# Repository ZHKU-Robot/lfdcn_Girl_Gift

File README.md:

# lfdcn_Girl_Gift

男生节即将结束，按照传统需要回馈女生礼物，故这次就制作礼物作为回馈(先占坑)

## 目录

- [更新](#更新)
- [示例](#示例)

## 更新

- 2020年11月18日23:39:10 yjc update 开场动画
- 2020年11月23日01:49:50 lfdcn update 原理图
- 2020年11月25日21:57:00 lfdcn update PCB&&Gerber

## 示例

### 原理图

### PCB

### 3D效果图

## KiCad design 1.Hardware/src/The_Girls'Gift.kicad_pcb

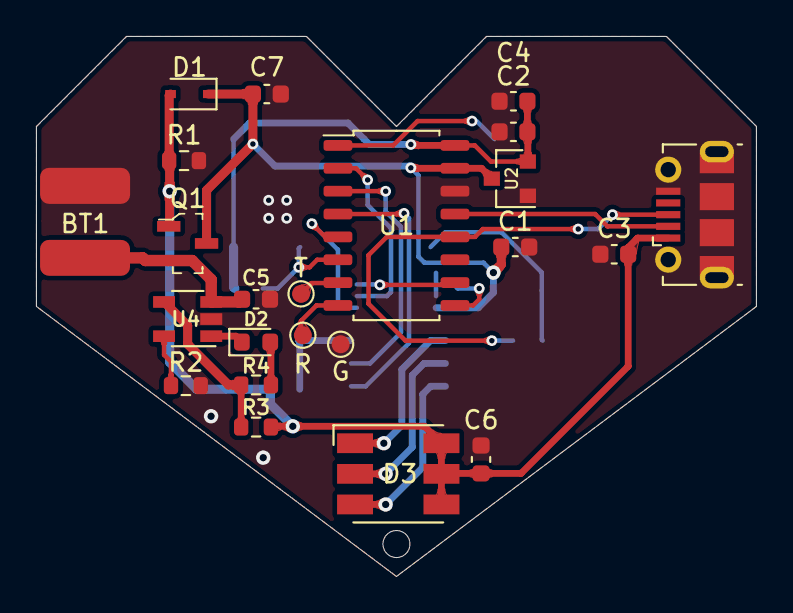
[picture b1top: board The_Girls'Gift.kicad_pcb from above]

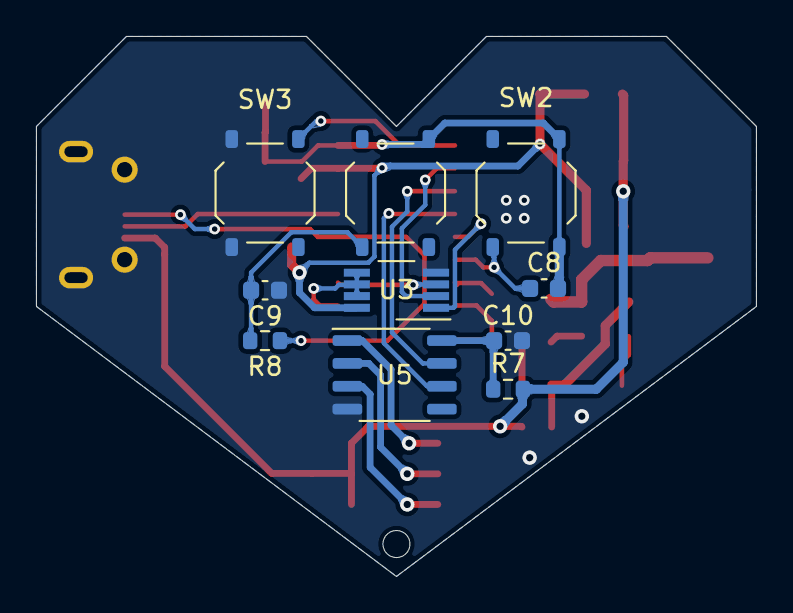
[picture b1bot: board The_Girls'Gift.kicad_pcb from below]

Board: 2 copper layers, 40.0 x 30.0 mm, 34 parts (10 on the bottom side), 26 nets.

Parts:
BT1: Battery_3.7V; Battery_Li_8x9x3mm
C1, C2, C3, C4, C5, C6, C7, C8, C10: 100nF; C_0603_1608Metric
C9: 47pF; C_0603_1608Metric
D1: 1N5817; D_SOD-323
D2: LED_R; LED_0603_1608Metric
D3: LED_RGB; LED_RGB_5050-6
G: TestPoint_Small; TestPoint_Pad_D1.0mm
H1: MountingHole; Via_1.5
J1: USB_B_Micro; USB_Micro-B_Molex-105017-0001
Q1: AO3401A; SOT-23-3
R: TestPoint_Small; TestPoint_Pad_D1.0mm
R1: 10k; R_0603_1608Metric
R2: 2K; R_0603_1608Metric
R3: 330R; R_0603_1608Metric
R4: 0.5Ω; R_0603_1608Metric
R7: 100; R_0603_1608Metric
R8: 10K; R_0603_1608Metric
SW1: Download; lfdcn_Button
SW2: RST; lfdcn_Button
SW3: USER; lfdcn_Button
T: TestPoint_Small; TestPoint_Pad_D1.0mm
U1: CH551G; SOP-16_4.55x10.3mm_P1.27mm
U2: 662K; SOT-23
U3: LM75B; VSSOP-8_3.0x3.0mm_P0.65mm
U4: 4054; TSOT-23-5
U5: MT3111; SOP-8_3.9x4.9mm_P1.27mm

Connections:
+3V3: C2.1, C4.2, C8.2, SW1.1, SW2.1, U1.16, U2.2
+5V: C3.2, C6.2, D1.2, D3.4, D3.5, D3.6, J1.1, Q1.1, R1.1, R4.2, R7.2
+BATT: BT1.1, C5.1, Q1.2, U4.3
/OUTB: D3.3, U5.3
/OUTG: D3.2, U5.2
/OUTR: D3.1, U5.1
/P11: U1.9, U3.5, U3.6, U3.7
/P14: U1.2, U3.2
/P15: U1.3, U5.7
/P16: U1.4, U5.6
/P17: U1.5, U3.1
/P30: R.1, U1.8
/P31: T.1, U1.7
/P32: SW3.1, U1.1
/P33: U1.10, U3.3
/P36: J1.3, R8.1, U1.12
/P37: J1.2, U1.13
/RST: C8.1, SW2.2, U1.6
GND: BT1.2, C1.2, C2.2, C3.1, C4.1, C5.2, C6.1, C7.1, C9.1, C10.2, G.1, J1.5, J1.6, R1.2, R2.1, SW3.2, U1.14, U2.1, U3.4, U4.2, U5.4
unnamed: C9.2, R8.2, SW1.2
unnamed: C10.1, R7.1, U5.8
unnamed: D2.1, U4.1
unnamed: D2.2, R3.1
unnamed: R2.2, U4.5
unnamed: R3.2, R4.1, U4.4
VCC: C1.1, C7.2, D1.1, Q1.3, U1.15, U2.3, U3.8

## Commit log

2020-11-18 随手做的一个开场动画
2020-11-22 master
2020-12-04 更新界面
2020-12-07 develop
